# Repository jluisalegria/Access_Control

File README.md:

# Access control with RFID reader. IoT Contest 2023 RT-Thread.

# Introduction
I made this project to participate in the IoT contest from RT-Thread.  
[RT-Thread](https://www.rt-thread.io/ "RT-Thread") is a tiny and elegant IoT Operating System.

RT-Thread Features
- Designed for resource-constrained devices, the minimum kernel requires only 1.2KB of RAM and 3 KB of Flash.
- Has rich components and a prosperous and fast growing package ecosystem.
- Elegant code style, easy to use, read and master.
- High Scalability. RT-Thread has high-quality scalable software architecture, loose coupling, modularity, is easy to tailor and expand.
- Supports high-performance applications.
- Supports cross-platform and a wide range of chips.

# Brief
On this project I create my own access control board with RFID wiegand 26 compatible.
There are too many comercial devices, but always the protocolo and software are close, and you have to use the software that the vendor have.
In my case I want to create this access control with the finality to add more functionalityes, for example, automatization of lights AAC control, proyectors, etc. When the people try to access to an area.
The main of this is for using in universities, thet have too many classrooms, in this first version yo can take control of the door, and you can control the light in the classroom using your RFID card. I want to add in a future second version a Led IR, to control more devices, like mini-splits, projectors and TV's.

# Hardware:
* CH32V208RBT6. I select this version because have a LQFP version. More easy to handsolder than the CH32V208WBU6 QFN.  
* RFID reader 125KHz. Modelo: PROID30-BE
* Relay Omron
* Eeprom I2C 2 MBits M24M02-DR M24M02-R
* RTC PCF8523

# Software:
* Code based on RT-Thread
* Own develop software "Sistema de control de acceso SICARFID"

# Wiring the Componets

|Reader  |Dev Board|
|--------|---------|
|Data 0  | PC9  |
|Data 1  | PC8  |
|Buzzer  | PC6  |
|Led     | PC7  |
|GND     | GND  |
|+5V     | +5V  |

|Relay   |Dev Board|
|--------|---------|
|RLY     | PB15 |
|+5V     | +5V  |

# TODO:
* Import the BSP from the repository for the WCH boards to make compile the project, with the toolchain RISC-V-GCC-WCH
* EEPROM Library
* RTC Library
* Routing
* Fab PCB

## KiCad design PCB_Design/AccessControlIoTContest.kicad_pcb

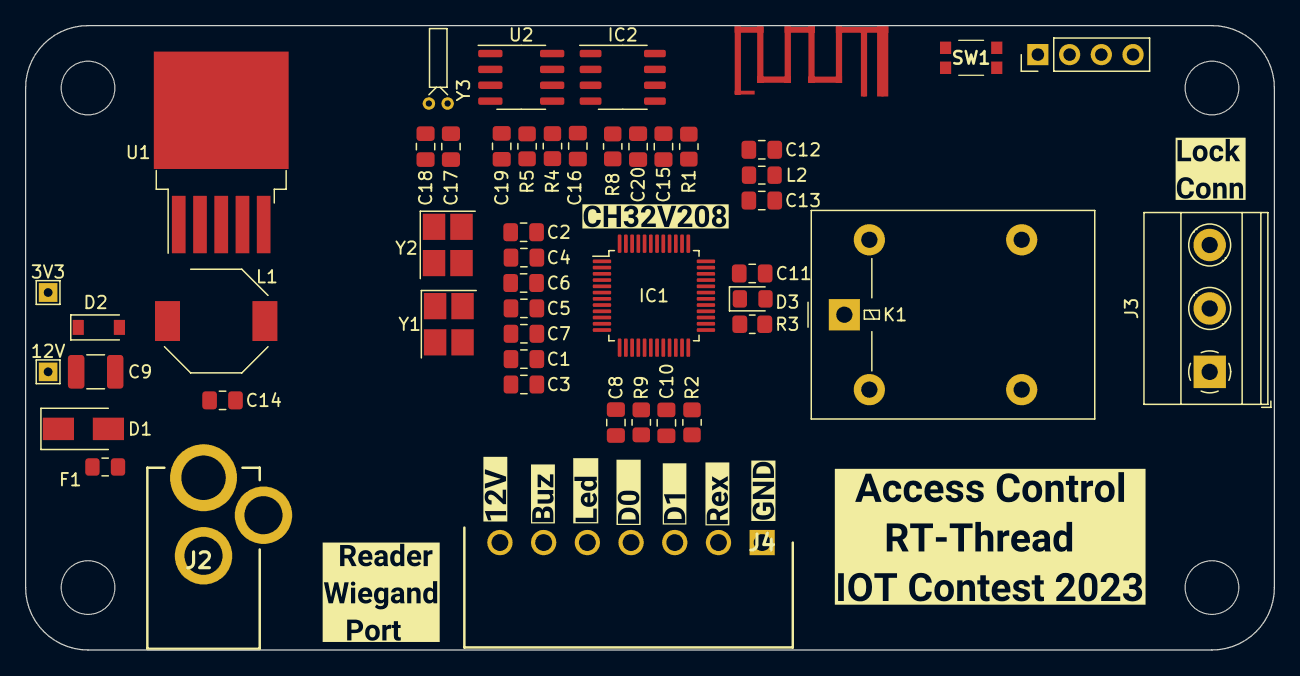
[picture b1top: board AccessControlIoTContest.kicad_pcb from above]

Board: 2 copper layers, 100.0 x 50.0 mm, 65 parts (1 on the bottom side), 35 nets, no tracks yet.

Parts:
3V3, 12V: TestPoint; TestPoint_THTPad_1.5x1.5mm_Drill0.7mm
AE1: Antenna; ANT-F-1-2.4G-0.2MM-FPC-WCH
C1, C2, C3, C4, C17, C18: 12pF; C_0805_2012Metric_Pad1.18x1.45mm_HandSolder
C5, C6, C7, C8, C10, C11, C16, C20: 0.1uF; C_0805_2012Metric_Pad1.18x1.45mm_HandSolder
C9: 100uF; C_1210_3225Metric_Pad1.33x2.70mm_HandSolder
C12, C13: 1pF; C_0805_2012Metric_Pad1.18x1.45mm_HandSolder
C14: 100uF; C_0805_2012Metric_Pad1.18x1.45mm_HandSolder
C15: 30pF; C_0805_2012Metric_Pad1.18x1.45mm_HandSolder
C19: 3.3uF; C_0805_2012Metric_Pad1.18x1.45mm_HandSolder
D1: B340A-E3_61T; D_SMA
D2: 1N5817; D_SOD-123
D3: Yellow; D_0805_2012Metric_Pad1.15x1.40mm_HandSolder
F1: 0ZCG0260BF2B; Fuse_0805_2012Metric_Pad1.15x1.40mm_HandSolder
H1, H2, H3, H4: MountingHole; MountingHole_4.3mm_M4
IC1: CH32V208RBT6; CH32V203C8T6_LQFP-48_7x7mm_P0.5mm
IC2: M24M02-DRMN6TP; SO-8_3.9x4.9mm_P1.27mm
J1: Conn_01x04_Male; PinHeader_1x04_P2.54mm_Vertical
J2: RAPC722X
J3: 1715031; TerminalBlock_Phoenix_MKDS-1,5-3-5.08_1x03_P5.08mm_Horizont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
J4: 39502-1007; SHDRRA7W80P0X350_1X7_2590X920X730P
K1: G5LE-1; Relay_SPDT_Omron-G5LE-1
L1: SRU8043-101Y; L_Bourns-SRU8028_8.0x8.0mm
L2: L_Small; L_0805_2012Metric_Pad1.15x1.40mm_HandSolder
R1, R2, R9: 10K; R_0805_2012Metric_Pad1.20x1.40mm_HandSolder
R3, R8: 1K; R_0805_2012Metric_Pad1.20x1.40mm_HandSolder
R4, R5: 4K; R_0805_2012Metric_Pad1.20x1.40mm_HandSolder
SW1: SW_Push; KMR621NGLFS
U1: GL2576-3.3TA5R; TO-263-5_TabPin3
U2: PCF8523T; SOIC-8_3.9x4.9mm_P1.27mm
U3: BAT-HLD-001; BatteryHolder_Keystone_3000_1x12mm
Y1, Y2: 32MHz; Crystal_SMD_SeikoEpson_FA238-4Pin_3.2x2.5mm_HandSoldering
Y3: 32.768KHz; Crystal_DS10_D1.0mm_L4.3mm_Horizontal
kibuzzard-64C431A8: G***; kibuzzard-64C431A8
kibuzzard-64C431B7: G***; kibuzzard-64C431B7
kibuzzard-64C431C2: G***; kibuzzard-64C431C2
kibuzzard-64C431CD: G***; kibuzzard-64C431CD
kibuzzard-64C431DA: G***; kibuzzard-64C431DA
kibuzzard-64C431EA: G***; kibuzzard-64C431EA
kibuzzard-64C4306F: G***; kibuzzard-64C4306F
kibuzzard-64C4325D: G***; kibuzzard-64C4325D
kibuzzard-64C43168: G***; kibuzzard-64C43168
kibuzzard-64C43228: G***; kibuzzard-64C43228
kibuzzard-64C43248: G***; kibuzzard-64C43248

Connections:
+3.3V: C8.1, C10.2, IC1.19 (VDD_VIO_4), IC1.32 (VDD_VIO_1), J1.4, SW1.2
+3V3: 3V3.1, C14.1, C16.1, C20.1, IC2.3 (E2), IC2.8 (VCC), K1.5, L1.2, R3.1, R4.1, R5.1, R8.1, R9.1, U1.4 (FB)
+12V: 12V.1, C9.1, D1.1, F1.2, J4.7, U1.1 (VIN)
/COM1: J3.2, K1.1
/NC1: J3.3, K1.4
/NO1: J3.1, K1.3
/OUT: D2.1 (K), L1.1, U1.2 (OUT)
Buzzer: IC1.37 (PC6/RXP), J4.6
DATA0: IC1.40 (PC9/TXN), J4.4
DATA1: IC1.39 (PC8/TXP), J4.3
GND: C1.1, C2.1, C3.1, C4.1, C5.1, C6.1, C7.1, C8.2, C9.2, C10.1, C11.2, C12.1, C13.1, C14.2, C15.2, C16.2, C17.2, C18.2, C19.1, C20.2, D1.2, D2.2 (A), IC1.5 (VSSA), IC1.18 (VSS_4), IC1.31 (VSS_1), IC2.1 (DU_1), IC2.2 (DU_2), IC2.4 (VSS), IC2.7 (~WC), J1.3, J2.1, J2.2, J4.1, R1.1, R2.2, U1.3 (GND), U1.5 (~ON/OFF), U2.4 (VSS), Y1.2, Y1.4, Y2.2, Y2.4
Led: IC1.38 (PC7/RXN), J4.5
unnamed: AE1.1 (A), C13.2, L2.2
unnamed: C5.2, IC1.8 (NRST)
unnamed: C6.2, IC1.1 (VBAT)
unnamed: C7.2, IC1.14 (PA0/WKUP/ADC0)
unnamed: C11.1, IC1.47 (VINTA)
unnamed: C12.2, IC1.48 (ANT), L2.1
unnamed: C17.1, U2.2 (OSCO), Y3.1
unnamed: C18.1, U2.1 (OSCI), Y3.2
unnamed: C19.2, R8.2, U2.8 (VDD)
unnamed: D3.2 (A), R3.2
unnamed: R1.2, SW1.1
unnamed: IC1.28 (PB2/BOOT1), R2.1
unnamed: U2.3 (VBAT), U3.1, U3.2
OSC32IN: C2.2, IC1.3 (PC14/OSC32IN), Y2.1
OSC32OUT: C4.2, IC1.4 (PC15/OSC32OUT), Y2.3
OSC_IN: C1.2, IC1.6 (OSC_IN), Y1.1
OSC_OUT: C3.2, IC1.7 (OSC_OUT), Y1.3
REX1: J4.2, R9.2
Relay: D3.1 (K), IC1.36 (PB15), K1.2
SCL: IC1.41 (PA8), IC2.6 (SCL), R4.2, U2.6 (SCL)
SDA: C15.1, IC1.42 (PA9), IC2.5 (SDA), R5.2, U2.5 (SDA)
SWDIO: IC1.46 (PA13/SWDIO), J1.1
VCC: F1.1, J2.3

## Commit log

2023-07-29 Edited README
2023-07-29 Edited images in README
